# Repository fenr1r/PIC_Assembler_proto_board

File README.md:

# PIC_Assembler_proto_board
A experimental board for the book "A First Course in the Microcontroller Programing with PICmicro"

### 概要

CQ出版社の「はじめてのPICアセンブラ入門」のための実験用ボード（本の中ではユニバーサル基板に組んでいる回路を、プリント基板にしたもの）

詳しくはブログをご覧ください :

https://vita-brevis.hatenablog.com/entry/2025/12/15/085609

秋月のBタイプ基板（95 x 72mm）サイズで、「B基板用アクリルパネル」に合うようにしました。

- DC入力は5V
- スイッチは秋月で販売している"2MS1-T1-B4-M7-Q-E-S"です
- ネジ・スペーサーはM3で、スペーサーは基板の下は高さ5mm、基板の上は高さ25mmを使いました

###### 本の回路図と違う点

- PICkit3用のコネクタの実装
    - ISPできるようにした
- 電源周り
    - スイッチなどを実装
- サーボモーター用電源、小型モーター用電源とPIC用電源を繋ぐジャンパを設置
   - サーボモーターくらいなら電源共用でも動きました

###### 未検証の点

- USB-Cコネクタ周り（給電用に設けたが、使わなかった）
- モータードライバー TA7291P 周り（小型モーターを手に入れる前に読んでしまったため、実装していない）

###### 設計ミス、工夫の足りなかった点

Githubでも書きましたが、少し設計ミスや、工夫の足りなかった点があります。
（いないと思いますけど）もし発注するのであれば、適宜直してください。

- UARTはRS-232出力となっているが、TTLレベルの出力も用意しておけばよかった（FTDIのUSB-UART変換で読めるから。わざわざUSB-RS232アダプタ持ち出さなくてもいい）
- ADC用のVRを半固定抵抗で実装したが、いちいちドライバーを用意して回すのは手間なので、可変抵抗にしておけばよかった
- LCDとC7が干渉する
   - C7を低背のものにすれば解消する
- PICkit3のピンヘッダとRS-232のコネクタも干渉するが、これはもう仕方ない
- SWの番号の違い（本だと回路図は1, 2だが、ソースコード上は0, 1である。正直私のせいではない…）
- PIC16F877Aをゼロプレッシャー実装する
   - 今の基板はISP書き込みを念頭に置いている。が、ライターを使うならゼロプレッシャーになると思う

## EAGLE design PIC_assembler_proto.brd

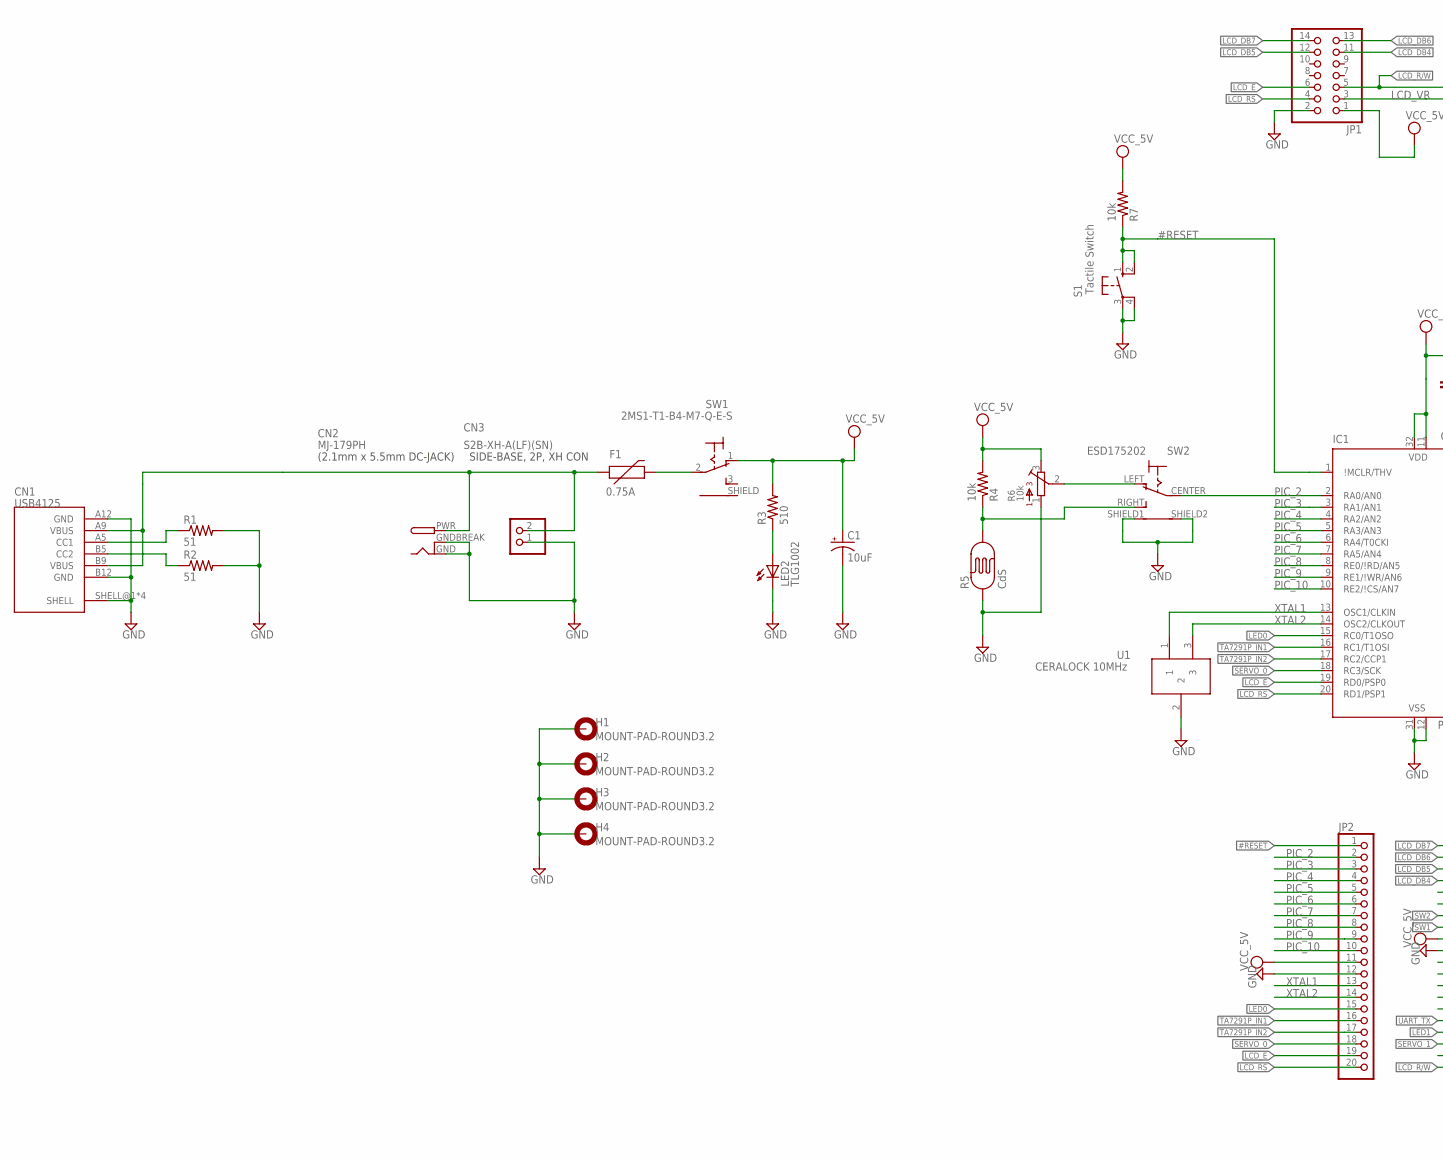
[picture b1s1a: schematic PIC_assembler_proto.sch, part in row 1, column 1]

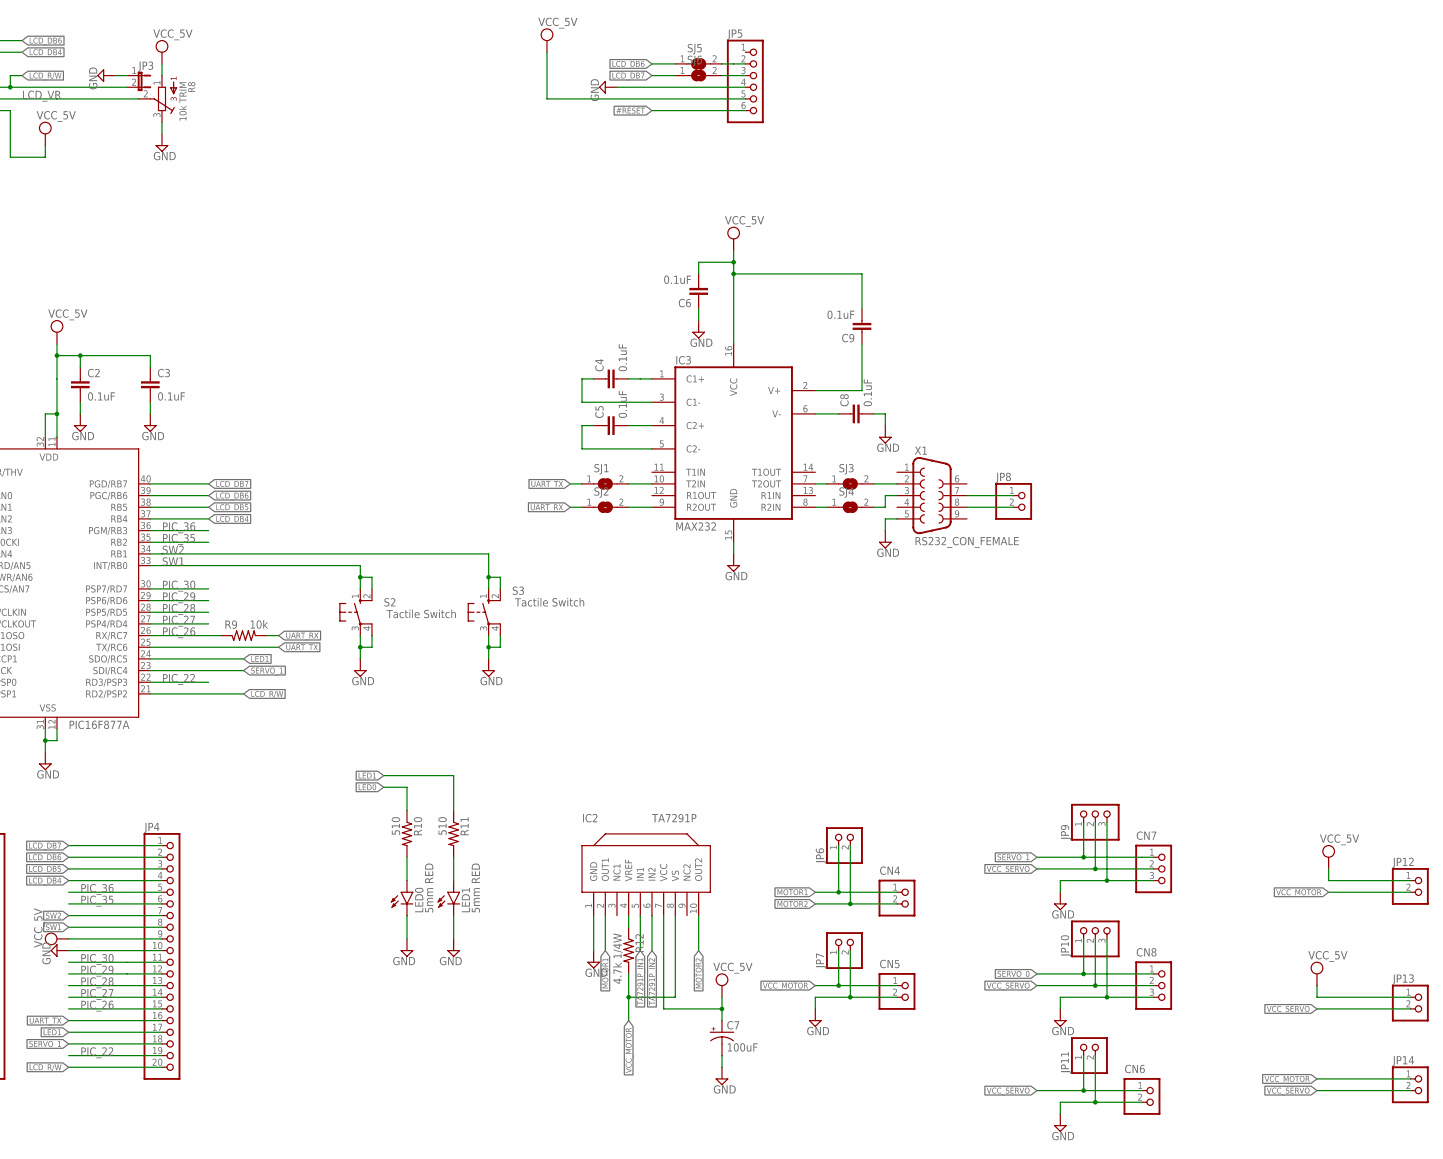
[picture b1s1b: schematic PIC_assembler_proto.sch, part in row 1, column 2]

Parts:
C1: 10uF; E2,5-7
C2, C3, C4, C5, C6, C8, C9: 0.1uF; C050-025X075
C7: 100uF; E2,5-7
CN1: USB4125; USB4215
CN2: MJ-179PH; DCJACK_2MM_THIN_18742
CN3: S2B-XH-A(LF)(SN); B2B-XH-A
CN4, CN5, CN6: S2B-XH-A
CN7, CN8: S3B-XH-A
F1: 0.75A; PTC
H1, H2, H3, H4: MOUNT-PAD-ROUND3.2; 3,2-PAD
IC1: PIC16F877A; DIL40
IC2: TA7291P; SIL10
IC3: MAX232; DIL16
JP1: PINHD-2X7; 2X07
JP2, JP4: PINHD-1X20; 1X20
JP3: JUMPER-2PTH; 1X02
JP5: PINHD-1X6/90; 1X06/90
JP6, JP7, JP8, JP11, JP12, JP13, JP14: PINHD-1X2; 1X02
JP9, JP10: PINHD-1X3; 1X03
LED0, LED1: 5mm RED; LED5MM
LED2: TLG1002; CHIPLED_0805
R1, R2: 51; R0603
R3, R10, R11: 510; 0207/10
R4, R7, R9: 10k; 0207/10
R5: CdS; PHOTOCELL
R6: 10k; 3362P
R8: 10k TRIM; 3362P
R12: 4.7k 1/4W; 0207/10
S1, S2, S3: Tactile Switch; B3F-10XX
SJ1, SJ2, SJ3, SJ4, SJ5, SJ6: SJ
SW1: 2MS1-T1-B4-M7-Q-E-S
SW2: ESD175202
U1: CERALOCK 10MHz; CERALOCK
X1: RS232_CON_FEMALE; DB9

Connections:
#RESET: IC1.1 (\!MCLR/THV), JP2.1, JP5.6, R7.1, S1.1 (S), S1.2 (S1)
GND: C1.-, C2.2, C3.2, C6.1, C7.-, C8.2, CN1.A12 (GND), CN1.B12 (GND), CN1.SHELL@1 (SHELL), CN1.SHELL@2 (SHELL), CN1.SHELL@3 (SHELL), CN1.SHELL@4 (SHELL), CN2.GND, CN2.GNDBREAK, CN3.1, CN5.2, CN6.2, CN7.3, CN8.3, H1.B3,2, H2.B3,2, H3.B3,2, H4.B3,2, IC1.12 (VSS), IC1.31 (VSS), IC2.1 (GND), IC3.15 (GND), JP1.2, JP2.12, JP3.1, JP4.10, JP5.4, JP7.2, JP9.3, JP10.3, JP11.2, LED0.K (C), LED1.K (C), LED2.C, R1.2, R2.2, R5.1, R6.1, R8.3, S1.3, S1.4 (P1), S2.3, S2.4 (P1), S3.3, S3.4 (P1), SW2.SHIELD1, SW2.SHIELD2, U1.2, X1.5
LCD_DB4: IC1.37 (RB4), JP1.11, JP4.4
LCD_DB5: IC1.38 (RB5), JP1.12, JP4.3
LCD_DB6: IC1.39 (PGC/RB6), JP1.13, JP4.2, SJ5.1
LCD_DB7: IC1.40 (PGD/RB7), JP1.14, JP4.1, SJ6.1
LCD_E: IC1.19 (RD0/PSP0), JP1.6, JP2.19
LCD_R/W: IC1.21 (RD2/PSP2), JP1.5, JP3.2, JP4.20
LCD_RS: IC1.20 (RD1/PSP1), JP1.4, JP2.20
LCD_VR: JP1.3, R8.2
LED0: IC1.15 (RC0/T1OSO), JP2.15, R10.1
LED1: IC1.24 (SDO/RC5), JP4.17, R11.1
MOTOR1: CN4.1, IC2.2 (OUT1), JP6.1
MOTOR2: CN4.2, IC2.10 (OUT2), JP6.2
unnamed: JP8.1, X1.7
unnamed: SJ3.2, X1.2
unnamed: IC3.9 (R2OUT), SJ2.2
unnamed: R4.1, R5.2, SW2.RIGHT (O2)
unnamed: R6.2, SW2.LEFT (O1)
unnamed: IC3.8 (R2IN), SJ4.1
unnamed: F1.P$2 (2), SW1.2 (2COMM)
unnamed: IC3.10 (T2IN), SJ1.2
unnamed: JP8.2, X1.8
unnamed: IC2.4 (VREF), R12.1
unnamed: JP5.2, SJ5.2
unnamed: IC3.7 (T2OUT), SJ3.1
unnamed: JP5.3, SJ6.2
unnamed: SJ4.2, X1.3
unnamed: LED0.A, R10.2
unnamed: LED1.A, R11.2
unnamed: C9.1, IC3.2 (V+)
unnamed: C8.1, IC3.6 (V-)
unnamed: C5.2, IC3.4 (C2+)
unnamed: C5.1, IC3.5 (C2-)
unnamed: C4.1, IC3.3 (C1-)
unnamed: C4.2, IC3.1 (C1+)
unnamed: CN1.A9 (VBUS), CN1.B9 (VBUS), CN2.PWR, CN3.2, F1.P$1 (1)
unnamed: LED2.A, R3.1
unnamed: CN1.B5 (CC2), R2.1
unnamed: CN1.A5 (CC1), R1.1
PIC_2: IC1.2 (RA0/AN0), JP2.2, SW2.CENTER (COMMON)
PIC_3: IC1.3 (RA1/AN1), JP2.3
PIC_4: IC1.4 (RA2/AN2), JP2.4
PIC_5: IC1.5 (RA3/AN3), JP2.5
PIC_6: IC1.6 (RA4/T0CKI), JP2.6
PIC_7: IC1.7 (RA5/AN4), JP2.7
PIC_8: IC1.8 (RE0/\!RD/AN5), JP2.8
PIC_9: IC1.9 (RE1/\!WR/AN6), JP2.9
PIC_10: IC1.10 (RE2/\!CS/AN7), JP2.10
PIC_22: IC1.22 (RD3/PSP3), JP4.19
PIC_26: IC1.26 (RX/RC7), JP4.15, R9.1
PIC_27: IC1.27 (PSP4/RD4), JP4.14
PIC_28: IC1.28 (PSP5/RD5), JP4.13
PIC_29: IC1.29 (PSP6/RD6), JP4.12
PIC_30: IC1.30 (PSP7/RD7), JP4.11
PIC_35: IC1.35 (RB2), JP4.6
PIC_36: IC1.36 (PGM/RB3), JP4.5
SERVO_0: CN8.1, IC1.18 (RC3/SCK), JP2.18, JP10.1
SERVO_1: CN7.1, IC1.23 (SDI/RC4), JP4.18, JP9.1
SW1: IC1.33 (INT/RB0), JP4.8, S2.1 (S), S2.2 (S1)
SW2: IC1.34 (RB1), JP4.7, S3.1 (S), S3.2 (S1)
TA7291P_IN1: IC1.16 (RC1/T1OSI), IC2.5 (IN1), JP2.16
TA7291P_IN2: IC1.17 (RC2/CCP1), IC2.6 (IN2), JP2.17
UART_RX: R9.2, SJ2.1
UART_TX: IC1.25 (TX/RC6), JP4.16, SJ1.1
VCC_5V: C1.+, C2.1, C3.1, C6.2, C7.+, C9.2, IC1.11 (VDD), IC1.32 (VDD), IC2.7 (VCC), IC3.16 (VCC), JP1.1, JP2.11, JP4.9, JP5.5, JP12.1, JP13.1, R3.2, R4.2, R6.3, R7.2, R8.1, SW1.1
VCC_MOTOR: CN5.1, IC2.8 (VS), JP7.1, JP12.2, JP14.1, R12.2
VCC_SERVO: CN6.1, CN7.2, CN8.2, JP9.2, JP10.2, JP11.1, JP13.2, JP14.2
XTAL1: IC1.13 (OSC1/CLKIN), JP2.13, U1.1
XTAL2: IC1.14 (OSC2/CLKOUT), JP2.14, U1.3

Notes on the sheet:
(2.1mm x 5.5mm DC-JACK)
SIDE-BASE, 2P, XH CON

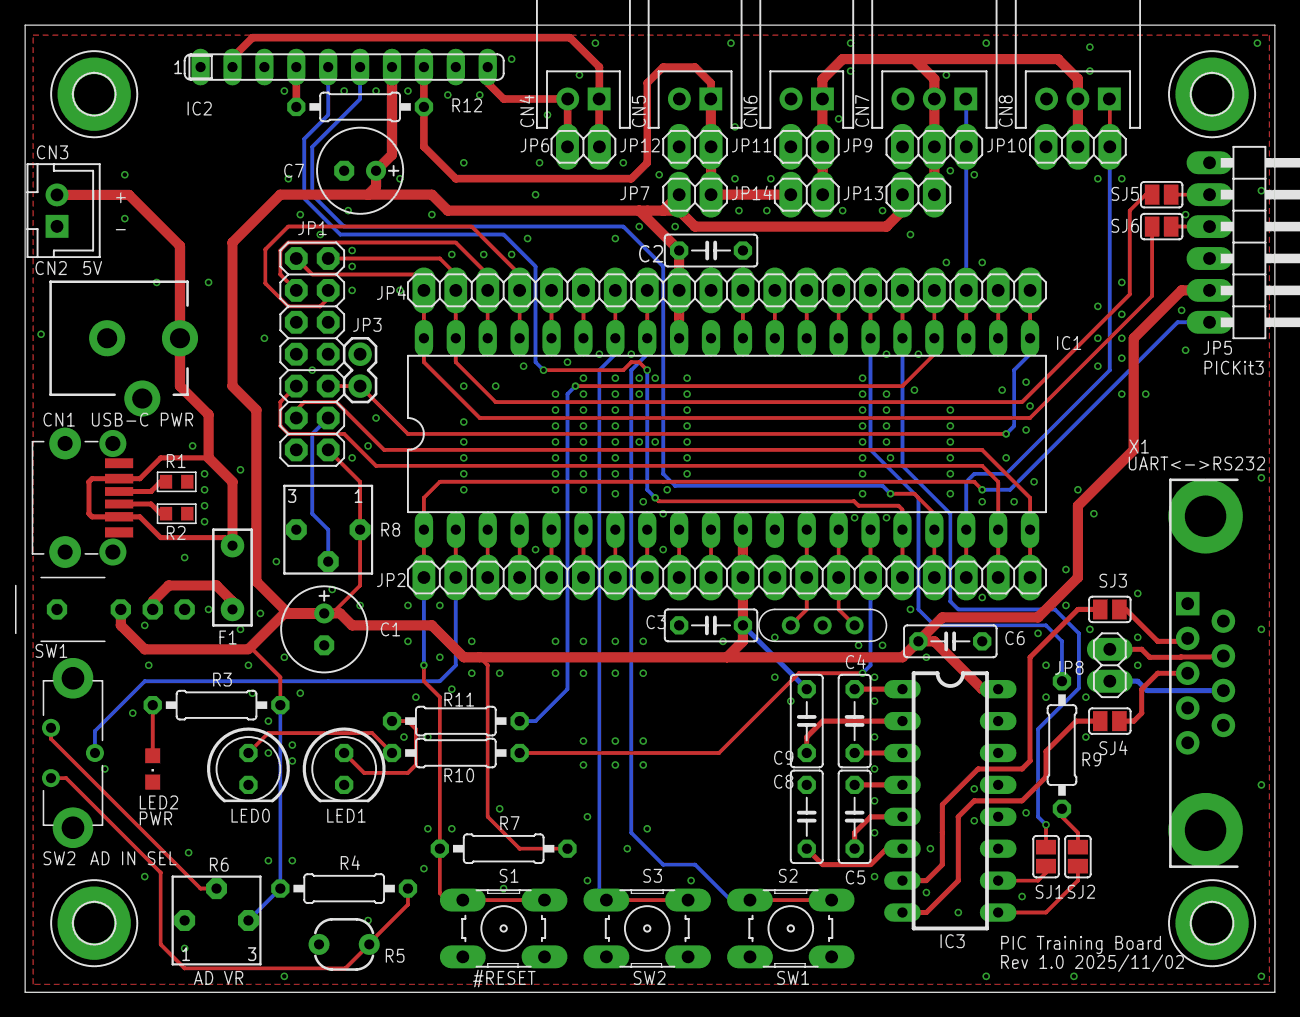
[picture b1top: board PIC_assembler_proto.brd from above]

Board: 2 copper layers, 99.5 x 77.0 mm, 67 parts (0 on the bottom side), 70 nets.

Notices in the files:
parts and their libraries:
SparkFun-PowerIC: Licensing: CC v3.0 Share-Alike You are welcome to use this library for commercial purposes.
